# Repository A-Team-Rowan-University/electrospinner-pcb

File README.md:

# electrospinner/pcb
PCB design for use in the electrospinner project

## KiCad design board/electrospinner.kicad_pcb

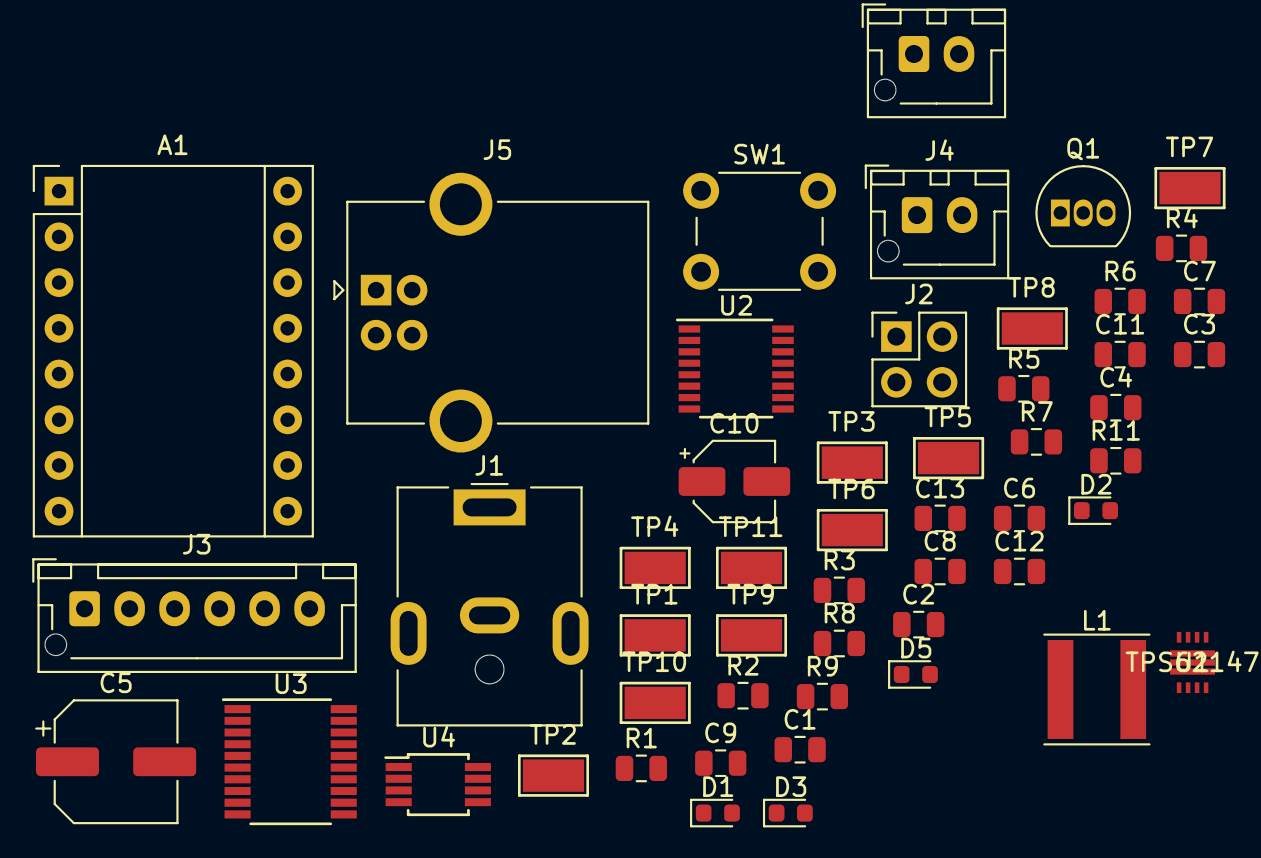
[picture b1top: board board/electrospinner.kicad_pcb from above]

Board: 2 copper layers, 52 parts (0 on the bottom side), 46 nets, no tracks yet.

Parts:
A1: DRV8825; Pololu_Breakout-16_15.2x20.3mm
C1: 10uF; C_0805_2012Metric
C2: 3.3uF; C_0805_2012Metric
C3, C4, C6, C7, C8, C9, C13: 0.1uF; C_0805_2012Metric
C5: 100uF; CP_Elec_6.3x5.8
C10: 1uF; CP_Elec_4x5.4
C11, C12: 22uF; C_0805_2012Metric
D1: LedRX; LED_0603_1608Metric
D2: LedTX; LED_0603_1608Metric
D3: LedRED; LED_0603_1608Metric
D5: LedGRN; LED_0603_1608Metric
J1: 12Vin; BarrelJack_CUI_PJ-063AH_Horizontal
J2: Programmer; PinHeader_2x02_P2.54mm_Vertical
J3: MotorConnector; JST_XH_B6B-XH-AM_1x06_P2.50mm_Vertical
J4: TempSensorConnector; JST_XH_B2B-XH-AM_1x02_P2.50mm_Vertical
J5: USB_B; USB_B_OST_USB-B1HSxx_Horizontal
J6: FanConnector; JST_XH_B2B-XH-AM_1x02_P2.50mm_Vertical
L1: 2.2uH; L_Coilcraft_XEL6030
Q1: 2N7000; TO-92_Inline
R1: 560k; R_0805_2012Metric
R2: 150k; R_0805_2012Metric
R3, R7: 75k; R_0805_2012Metric
R4: 10k; R_0805_2012Metric
R5, R6, R9, R11: 390; R_0805_2012Metric
R8: 1M; R_0805_2012Metric
SW1: ResetBTN; SW_PUSH_6mm_H5mm
TP1: ~MotorRST; TestPoint_Keystone_5015_Micro-Minature
TP2: ~MotorEN; TestPoint_Keystone_5015_Micro-Minature
TP3: ~MotorSLP; TestPoint_Keystone_5015_Micro-Minature
TP4: MotorDIR; TestPoint_Keystone_5015_Micro-Minature
TP5: ~MotorFLT; TestPoint_Keystone_5015_Micro-Minature
TP6: PCB_TX; TestPoint_Keystone_5015_Micro-Minature
TP7: PCB_RX; TestPoint_Keystone_5015_Micro-Minature
TP8: MotorM0; TestPoint_Keystone_5015_Micro-Minature
TP9: MotorM1; TestPoint_Keystone_5015_Micro-Minature
TP10: MotorM2; TestPoint_Keystone_5015_Micro-Minature
TP11: MotorSTEP; TestPoint_Keystone_5015_Micro-Minature
U1: TPS62147; TPS62147RGXR
U2: FT230XS; SSOP-16_3.9x4.9mm_P0.635mm
U3: MSP430G2553IPW20; TSSOP-20_4.4x6.5mm_P0.65mm
U4: AD8495; MSOP-8_3x3mm_P0.65mm

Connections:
+3V3: C4.1, C6.1, C7.1, C8.1, C11.1, C12.1, J2.1, L1.2, R1.1, R4.1, R5.1, R6.1, U1.6
+12V: C3.1, C5.1, J1.1, Q1.3
/A1: A1.4, J3.1
/A2: A1.3, J3.3
/B1: A1.5, J3.4
/B2: A1.6, J3.6
/D+: J5.3, U2.8
/D-: J5.2, U2.9
/FAN: Q1.2, U3.7
/LedGRN: D5.2, U3.6, U3.15
/LedRED: D3.2, U3.5
/MotorDIR: A1.16, TP4.1, U3.11
/MotorM0: A1.10, TP8.1, U3.13
/MotorM1: A1.11, TP9.1, U3.19
/MotorM2: A1.12, TP10.1, U3.18
/MotorSTEP: A1.15, TP11.1, U3.14
/PCB_RX: TP7.1, U2.4, U3.4
/PCB_TX: TP6.1, U2.1, U3.3
/TEST: J2.3, U3.17
/Vo,temp: U3.2, U4.5, U4.6
/~LedRX: D1.1, U2.14
/~LedTX: D2.1, U2.7
/~MotorEN: A1.9, TP2.1, U3.9
/~MotorFLT: A1.2, TP5.1, U3.12
/~MotorRST: A1.13, TP1.1, U3.8
/~MotorSLP: A1.14, TP3.1, U3.10
/~RST: J2.4, R4.2, SW1.2, U2.11, U3.16
GND: A1.1, A1.7, C1.2, C2.2, C9.1, C11.2, C12.2, C13.2, J1.2, J1.MP, J2.2, J5.4, J5.5, J6.2, R2.2, R8.1, R9.1, R11.1, SW1.1, U1.3, U1.4, U1.7, U1.10, U1.11, U2.5, U2.13, U3.20, U4.2, U4.3
unnamed: A1.8, C5.2
unnamed: C1.1, C3.2, U1.1, U1.8
unnamed: C2.1, U1.9
unnamed: C4.2, U4.7
unnamed: C6.2, U3.1
unnamed: C7.2, U2.12
unnamed: C8.2, U2.3
unnamed: C9.2, C10.1, R3.2, U4.1
unnamed: C10.2, C13.1, R7.2, U4.8
unnamed: D1.2, R5.2
unnamed: D2.2, R6.2
unnamed: D3.1, R9.2
unnamed: D5.1, R11.2
unnamed: J4.1, R3.1, R8.2
unnamed: J4.2, R7.1
unnamed: J6.1, Q1.1
unnamed: L1.1, U1.2
unnamed: R1.2, R2.1, U1.5

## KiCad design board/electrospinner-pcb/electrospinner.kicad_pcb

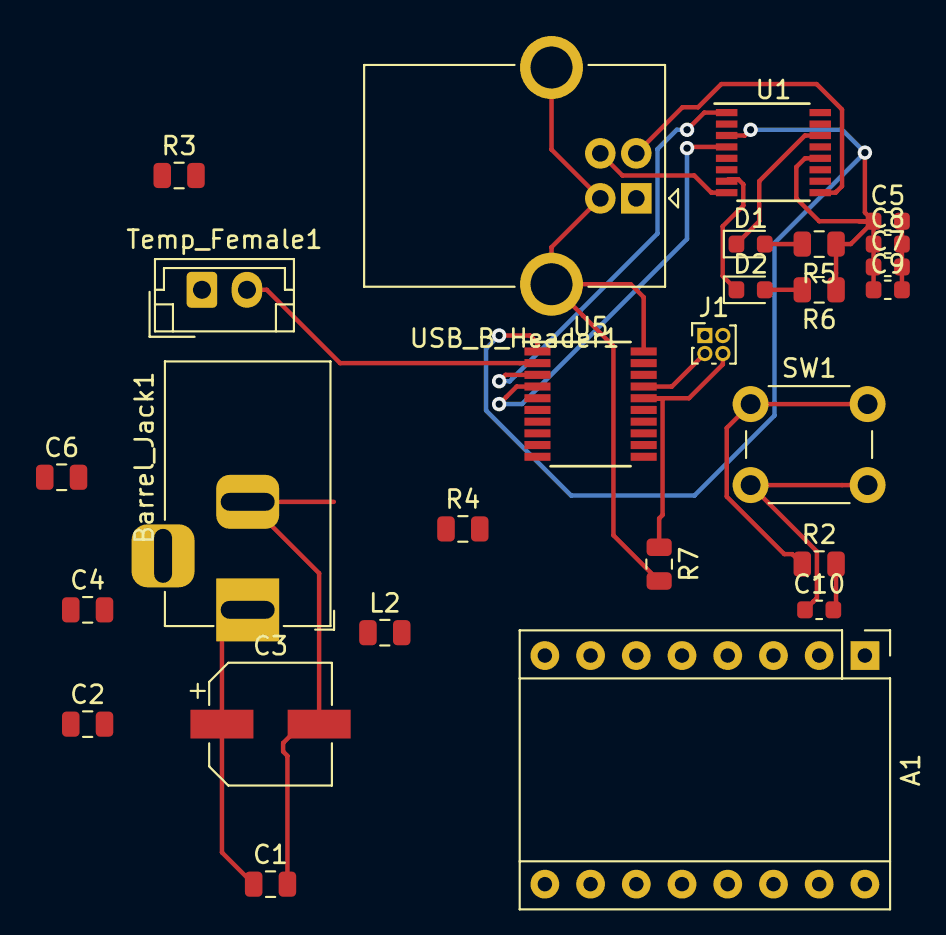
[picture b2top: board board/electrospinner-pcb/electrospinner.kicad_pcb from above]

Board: 2 copper layers, 27 parts (0 on the bottom side), 16 nets.

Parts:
A1: A4988_Breakout; Pololu_Breakout-16_15.2x20.3mm
Barrel_Jack1: BarrelJack; BarrelJack_Horizontal
C1: 0.1uF; C_0805_2012Metric
C2: 10uF; C_0805_2012Metric
C3: 100uF; CP_Elec_6.3x5.8
C4: 3.3uF; C_0805_2012Metric
C5, C7, C8, C9, C10: 0.1uF; C_0603_1608Metric
C6: 2.2uF; C_0805_2012Metric
D1: RXLED; LED_0603_1608Metric
D2: TXLED; LED_0603_1608Metric
J1: Header_02x02; PinHeader_2x02_P1.00mm_Vertical
L2: 1uH; L_0805_2012Metric
R2: 100; R_0805_2012Metric
R3: 560k; R_0805_2012Metric
R4: 150k; R_0805_2012Metric
R5, R6: 390; R_0805_2012Metric
R7: 10k; R_0805_2012Metric
SW1: ResetBTN; SW_PUSH_6mm_H5mm
Temp_Female1: JST_1x2_Female; JST_EH_B02B-EH-A_1x02_P2.50mm_Vertical
U1: FT230XS; SSOP-16_3.9x4.9mm_P0.635mm
U5: MSP430G2553IPW20; TSSOP-20_4.4x6.5mm_P0.65mm
USB_B_Header1: USB_B_Header?; USB_B_OST_USB-B1HSxx_Horizontal

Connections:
+3V3: A1.2, C5.1, C6.1, C7.1, C8.1, C9.1, C10.1, L2.2, R3.1, R5.1, R6.1, SW1.2, Temp_Female1.1, U1.3, U1.12, U5.1
+12V: A1.8, Barrel_Jack1.1, C1.1, C2.1, C3.1
/D+: U1.8, USB_B_Header1.3
/D-: U1.9, USB_B_Header1.2
/PCB_RX: U1.4, U5.4
/PCB_TX: U1.1, U5.3
/TEST: J1.3, U5.17
/Vo,temp: Temp_Female1.2, U5.2
/~RST: J1.4, R2.1, R7.1, SW1.1, U1.11, U5.16
/~RXLED: D1.1, U1.14
/~TXLED: D2.1, U1.7
GNDD: A1.1, A1.7, Barrel_Jack1.2, C1.2, C2.2, C3.2, C4.2, C5.2, C6.2, C7.2, C8.2, C9.2, R4.2, R7.2, U1.5, U1.13, U5.20, USB_B_Header1.4, USB_B_Header1.5
unnamed: C10.2, R2.2
unnamed: D1.2, R5.2
unnamed: D2.2, R6.2
unnamed: R3.2, R4.1

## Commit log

2019-03-14 Converts diptrace schematic to pdf
2019-03-17 Adds new schematic and bill or materials
2019-03-20 Adds all footprints
2019-03-20 Adds last of the footprints to pcb layout
2019-03-20 Removes sense resistors from stepper driver
2019-03-20 Updates footprints, adds bom
2019-03-21 Updates BOM and footprints, adds spreadsheet
2019-03-22 Saves schematic rev 1
2019-03-22 Changes files to dos compatibility line endings
2019-03-22 Converts all board files to dos
2019-03-25 Half-done finishing v2 of schematic
2019-03-25 Finishes rev2 of schematic
2019-03-25 Updates electrospinner.pdf
2019-03-26 Updates electrospinner.xlsx
2019-03-26 Fixes typo: ~MotorRESET
2019-04-08 Updates datasheets
    Adds camera datasheet
    Updates new stepper motor driver datasheet
2019-04-08 Updates board to rev 3
    Updates thematic
    Updates bom
2019-04-09 Updates electrospinner.pdf for rev3
2019-04-09 Updates electrospinner.net for rev3
2019-04-09 Updates bom and kicost for rev3
2019-04-10 Updates to rev5
2019-04-10 Cleans up board file structure
2019-04-10 Re-updates rev5 files
    Adds labels to schematic
    Renames uart.pdf to usb_to_uart.pdf
2019-04-11 Updates schematic for rev6
2019-04-11 Updates the BOM and layout for rev6
2019-04-18 Updates for rev7
    Adds project specific symbol and footprint libraries
    Adds thermocouple_amplifier datasheet
2019-05-20 Add files via upload
    converted schematic to diptrace

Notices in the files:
parts and their libraries:
Copyright 2016 Accelerated Designs. All rights reserved.
